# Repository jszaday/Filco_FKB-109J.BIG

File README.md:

# Universa Universis
Retrofit PCB for various Alps full-sized keyboards.

## Planned support:
- AEK (ANSI, EUR, JPN)
- DELL AT101W (ANSI, EUR, JPN)
- DELL AT101 (ANSI, EUR, JPN)
- Strong Man SMK-8851 (BAE, JPN)

## Version History:

### Alpha Revision

Front:

Back:

#### Known Issues
- DELL AT101 support impeded by unpopable popout between RAlt and RCtrl.
- ISO Enter in wrong position (1.5u vs. 1u); can fold down leads of switch to compensate.
- Num pad plus and enter key switches rotated 180° (not a significant issue).
- No LED carrier board.

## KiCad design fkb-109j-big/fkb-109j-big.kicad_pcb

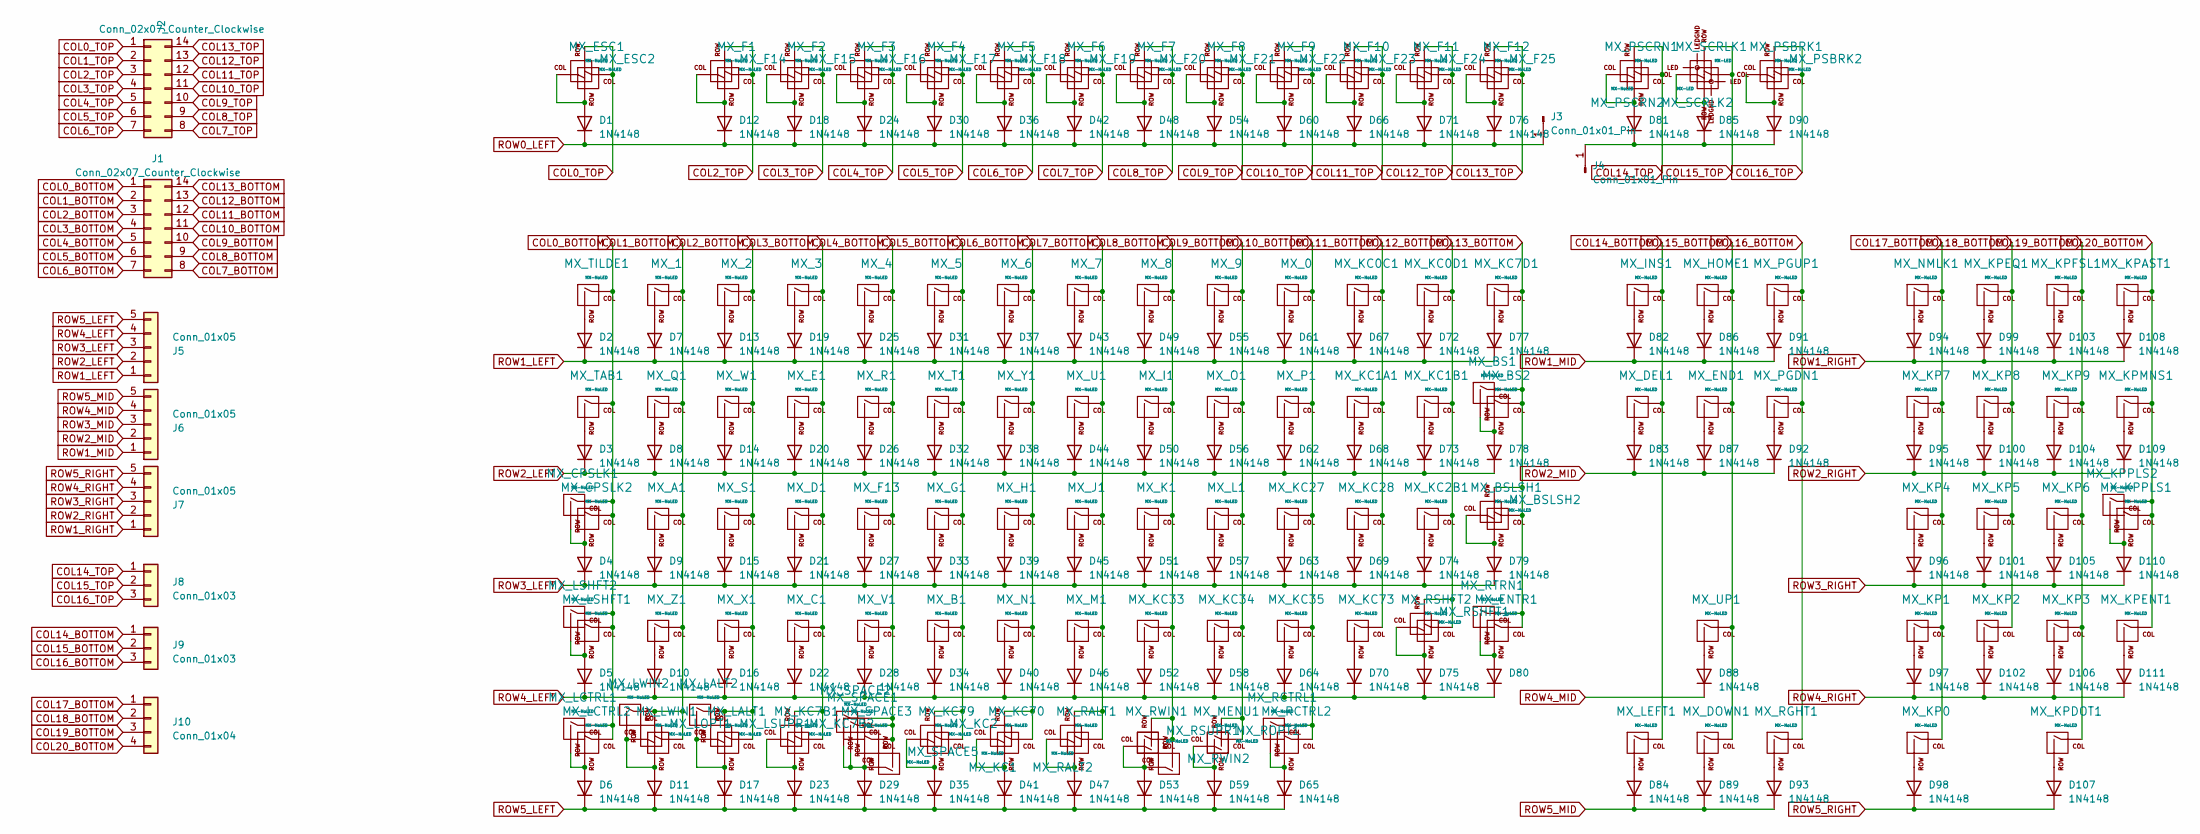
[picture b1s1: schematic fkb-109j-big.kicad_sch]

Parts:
D1, D2, D3, D4, D5, D6, D7, D8, D9, D10, D11, D12, D13, D14, D15, D16, D17, D18, D19, D20, D21, D22, D23, D24, D25, D26, D27, D28, D29, D30, D31, D32, D33, D34, D35, D36, D37, D38, D39, D40, D41, D42, D43, D44, D45, D46, D47, D48, D49, D50, D51, D52, D53, D54, D55, D56, D57, D58, D59, D60, D61, D62, D63, D64, D65, D66, D67, D68, D69, D70, D71, D72, D73, D74, D75, D76, D77, D78, D79, D80, D81, D82, D83, D84, D85, D86, D87, D88, D89, D90, D91, D92, D93, D94, D95, D96, D97, D98, D99, D100, D101, D102, D103, D104, D105, D106, D107, D108, D109, D110, D111: 1N4148; D_DO-35_SOD27_P7.62mm_Horizontal
J1, J2: Conn_02x07_Counter_Clockwise; PinHeader_1x14_P2.00mm_Vertical
J3, J4: Conn_01x01_Pin; PinHeader_1x01_P2.00mm_Vertical
J5, J6, J7: Conn_01x05; PinHeader_1x05_P2.00mm_Vertical
J8, J9: Conn_01x03; PinHeader_1x03_P2.00mm_Vertical
J10: Conn_01x04; PinHeader_1x04_P2.00mm_Vertical
MX_0, MX_1, MX_2, MX_3, MX_4, MX_5, MX_6, MX_7, MX_8, MX_9: MX-NoLED; ALPS-1U
MX_A1: MX-NoLED; ALPS-1U
MX_B1: MX-NoLED; ALPS-1U
MX_BS1: MX-NoLED; ALPS-1U
MX_BS2: MX-NoLED; ALPS-2U
MX_BSLSH1: MX-NoLED; ALPS-1.5U
MX_BSLSH2: MX-NoLED; ALPS-1U
MX_C1: MX-NoLED; ALPS-1U
MX_CPSLK1: MX-NoLED; ALPS-1.5U
MX_CPSLK2: MX-NoLED; ALPS-1.75U
MX_D1: MX-NoLED; ALPS-1U
MX_DEL1: MX-NoLED; ALPS-1U
MX_DOWN1: MX-NoLED; ALPS-1U
MX_E1: MX-NoLED; ALPS-1U
MX_END1: MX-NoLED; ALPS-1U
MX_ENTR1: MX-NoLED; ALPS-2U
MX_ESC1, MX_ESC2: MX-NoLED; ALPS-1U
MX_F1, MX_F2, MX_F3, MX_F4, MX_F5, MX_F6, MX_F7, MX_F8, MX_F9, MX_F10, MX_F11, MX_F12, MX_F13, MX_F14, MX_F15, MX_F16, MX_F17, MX_F18, MX_F19, MX_F20, MX_F21, MX_F22, MX_F23, MX_F24, MX_F25: MX-NoLED; ALPS-1U
MX_G1: MX-NoLED; ALPS-1U
MX_H1: MX-NoLED; ALPS-1U
MX_HOME1: MX-NoLED; ALPS-1U
MX_I1: MX-NoLED; ALPS-1U
MX_INS1: MX-NoLED; ALPS-1U
MX_J1: MX-NoLED; ALPS-1U
MX_K1: MX-NoLED; ALPS-1U
MX_KC0C1, MX_KC0D1, MX_KC1A1, MX_KC1B1, MX_KC2B1, MX_KC7D1, MX_KC27, MX_KC28, MX_KC33, MX_KC34, MX_KC35, MX_KC73: MX-NoLED; ALPS-1U
MX_KC1: MX-NoLED; ALPS-1.5U
MX_KC2, MX_KC7B2: MX-NoLED; ALPS-1.75U
MX_KC7B1, MX_KC70, MX_KC79: MX-NoLED; ALPS-1.25U
MX_KP0: MX-NoLED; ALPS-2U
MX_KP1, MX_KP2, MX_KP3, MX_KP4, MX_KP5, MX_KP6, MX_KP7, MX_KP8, MX_KP9: MX-NoLED; ALPS-1U
MX_KPAST1: MX-NoLED; ALPS-1U
MX_KPDOT1: MX-NoLED; ALPS-1U
MX_KPENT1: MX-NoLED; ALPS-2U
MX_KPEQ1: MX-NoLED; ALPS-1U
MX_KPFSL1: MX-NoLED; ALPS-1U
MX_KPMNS1: MX-NoLED; ALPS-1U
MX_KPPLS1: MX-NoLED; ALPS-1U
MX_KPPLS2: MX-NoLED; ALPS-2U
MX_L1: MX-NoLED; ALPS-1U
MX_LALT1: MX-NoLED; ALPS-1.25U
MX_LALT2: MX-NoLED; ALPS-1.5U
MX_LCTRL1: MX-NoLED; ALPS-1.25U
MX_LCTRL2: MX-NoLED; ALPS-1.5U
MX_LEFT1: MX-NoLED; ALPS-1U
MX_LOPT1: MX-NoLED; ALPS-1.25U
MX_LSHFT1: MX-NoLED; ALPS-2.25U
MX_LSHFT2: MX-NoLED; ALPS-1.25U
MX_LSUPR1: MX-NoLED; ALPS-1.5U
MX_LWIN1: MX-NoLED; ALPS-1.25U
MX_LWIN2: MX-NoLED; ALPS-1U
MX_M1: MX-NoLED; ALPS-1U
MX_MENU1: MX-NoLED; ALPS-1.25U
MX_N1: MX-NoLED; ALPS-1U
MX_NMLK1: MX-NoLED; ALPS-1U
MX_O1: MX-NoLED; ALPS-1U
MX_P1: MX-NoLED; ALPS-1U
MX_PGDN1: MX-NoLED; ALPS-1U
MX_PGUP1: MX-NoLED; ALPS-1U
MX_PSBRK1, MX_PSBRK2: MX-NoLED; ALPS-1U
MX_PSCRN1, MX_PSCRN2: MX-NoLED; ALPS-1U
MX_Q1: MX-NoLED; ALPS-1U
MX_R1: MX-NoLED; ALPS-1U
MX_RALT1: MX-NoLED; ALPS-1.25U
MX_RALT2: MX-NoLED; ALPS-1.5U
MX_RCTRL1: MX-NoLED; ALPS-1.25U
MX_RCTRL2: MX-NoLED; ALPS-1.5U
MX_RGHT1: MX-NoLED; ALPS-1U
MX_ROPT1: MX-NoLED; ALPS-1.25U
MX_RSHFT1: MX-NoLED; ALPS-2.75U
MX_RSHFT2: MX-NoLED; ALPS-1.75U
MX_RSUPR1: MX-NoLED; ALPS-1.5U
MX_RTRN1: MX-NoLED; ALPS-2.25U
MX_RWIN1: MX-NoLED; ALPS-1.25U
MX_RWIN2: MX-NoLED; ALPS-1U
MX_S1: MX-NoLED; ALPS-1U
MX_SCRLK1, MX_SCRLK2: MX-LED; ALPS-1U
MX_SPACE1: MX-NoLED; ALPS-6.5U
MX_SPACE2: MX-NoLED; ALPS-6.25U
MX_SPACE3: MX-NoLED; ALPS-2.5U
MX_SPACE5: MX-NoLED; ALPS-2U
MX_T1: MX-NoLED; ALPS-1U
MX_TAB1: MX-NoLED; ALPS-1.5U
MX_TILDE1: MX-NoLED; ALPS-1U
MX_U1: MX-NoLED; ALPS-1U
MX_UP1: MX-NoLED; ALPS-1U
MX_V1: MX-NoLED; ALPS-1U
MX_W1: MX-NoLED; ALPS-1U
MX_X1: MX-NoLED; ALPS-1U
MX_Y1: MX-NoLED; ALPS-1U
MX_Z1: MX-NoLED; ALPS-1U

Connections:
COL0_BOTTOM: J1.1, MX_CPSLK1.1 (COL), MX_CPSLK2.1 (COL), MX_LCTRL1.1 (COL), MX_LCTRL2.1 (COL), MX_LSHFT1.1 (COL), MX_LSHFT2.1 (COL), MX_TAB1.1 (COL), MX_TILDE1.1 (COL)
COL0_TOP: J2.1, MX_ESC1.1 (COL), MX_ESC2.2 (ROW)
COL1_BOTTOM: J1.2, MX_1.1 (COL), MX_A1.1 (COL), MX_LOPT1.2 (ROW), MX_LWIN1.1 (COL), MX_LWIN2.1 (COL), MX_Q1.1 (COL), MX_Z1.1 (COL)
COL1_TOP: J2.2
COL2_BOTTOM: J1.3, MX_2.1 (COL), MX_LALT1.1 (COL), MX_LALT2.1 (COL), MX_LSUPR1.2 (ROW), MX_S1.1 (COL), MX_W1.1 (COL), MX_X1.1 (COL)
COL2_TOP: J2.3, MX_F1.1 (COL), MX_F14.2 (ROW)
COL3_BOTTOM: J1.4, MX_3.1 (COL), MX_C1.1 (COL), MX_D1.1 (COL), MX_E1.1 (COL), MX_KC7B1.1 (COL), MX_KC7B2.2 (ROW)
COL3_TOP: J2.4, MX_F2.1 (COL), MX_F15.2 (ROW)
COL4_BOTTOM: J1.5, MX_4.1 (COL), MX_F13.1 (COL), MX_R1.1 (COL), MX_SPACE1.1 (COL), MX_SPACE2.1 (COL), MX_SPACE3.1 (COL), MX_SPACE5.2 (ROW), MX_V1.1 (COL)
COL4_TOP: J2.5, MX_F3.1 (COL), MX_F16.2 (ROW)
COL5_BOTTOM: J1.6, MX_5.1 (COL), MX_B1.1 (COL), MX_G1.1 (COL), MX_KC2.2 (ROW), MX_KC79.1 (COL), MX_T1.1 (COL)
COL5_TOP: J2.6, MX_F4.1 (COL), MX_F17.2 (ROW)
COL6_BOTTOM: J1.7, MX_6.1 (COL), MX_H1.1 (COL), MX_KC1.2 (ROW), MX_KC70.1 (COL), MX_N1.1 (COL), MX_Y1.1 (COL)
COL6_TOP: J2.7, MX_F5.1 (COL), MX_F18.2 (ROW)
COL7_BOTTOM: J1.8, MX_7.1 (COL), MX_J1.1 (COL), MX_M1.1 (COL), MX_RALT1.1 (COL), MX_RALT2.2 (ROW), MX_U1.1 (COL)
COL7_TOP: J2.8, MX_F6.1 (COL), MX_F19.2 (ROW)
COL8_BOTTOM: J1.9, MX_8.1 (COL), MX_I1.1 (COL), MX_K1.1 (COL), MX_KC33.1 (COL), MX_RSUPR1.2 (ROW), MX_RWIN1.1 (COL), MX_RWIN2.2 (ROW)
COL8_TOP: J2.9, MX_F7.1 (COL), MX_F20.2 (ROW)
COL9_BOTTOM: J1.10, MX_9.1 (COL), MX_KC34.1 (COL), MX_L1.1 (COL), MX_MENU1.1 (COL), MX_O1.1 (COL), MX_ROPT1.2 (ROW)
COL9_TOP: J2.10, MX_F8.1 (COL), MX_F21.2 (ROW)
COL10_BOTTOM: J1.11, MX_0.1 (COL), MX_KC27.1 (COL), MX_KC35.1 (COL), MX_P1.1 (COL), MX_RCTRL1.1 (COL), MX_RCTRL2.1 (COL)
COL10_TOP: J2.11, MX_F9.1 (COL), MX_F22.2 (ROW)
COL11_BOTTOM: J1.12, MX_KC0C1.1 (COL), MX_KC1A1.1 (COL), MX_KC28.1 (COL), MX_KC73.1 (COL)
COL11_TOP: J2.12, MX_F10.1 (COL), MX_F23.2 (ROW)
COL12_BOTTOM: J1.13, MX_KC0D1.1 (COL), MX_KC1B1.1 (COL), MX_KC2B1.1 (COL), MX_RSHFT1.2 (ROW), MX_RSHFT2.1 (COL)
COL12_TOP: J2.13, MX_F11.1 (COL), MX_F24.2 (ROW)
COL13_BOTTOM: J1.14, MX_BS1.1 (COL), MX_BS2.1 (COL), MX_BSLSH1.1 (COL), MX_BSLSH2.2 (ROW), MX_ENTR1.1 (COL), MX_KC7D1.1 (COL), MX_RTRN1.1 (COL)
COL13_TOP: J2.14, MX_F12.1 (COL), MX_F25.2 (ROW)
COL14_BOTTOM: J9.1, MX_DEL1.1 (COL), MX_INS1.1 (COL), MX_LEFT1.1 (COL)
COL14_TOP: J8.1, MX_PSCRN1.1 (COL), MX_PSCRN2.2 (ROW)
COL15_BOTTOM: J9.2, MX_DOWN1.1 (COL), MX_END1.1 (COL), MX_HOME1.1 (COL), MX_UP1.1 (COL)
COL15_TOP: J8.2, MX_SCRLK1.1 (COL), MX_SCRLK2.2 (ROW)
COL16_BOTTOM: J9.3, MX_PGDN1.1 (COL), MX_PGUP1.1 (COL), MX_RGHT1.1 (COL)
COL16_TOP: J8.3, MX_PSBRK1.1 (COL), MX_PSBRK2.2 (ROW)
COL17_BOTTOM: J10.1, MX_KP0.1 (COL), MX_KP1.1 (COL), MX_KP4.1 (COL), MX_KP7.1 (COL), MX_NMLK1.1 (COL)
COL18_BOTTOM: J10.2, MX_KP2.1 (COL), MX_KP5.1 (COL), MX_KP8.1 (COL), MX_KPEQ1.1 (COL)
COL19_BOTTOM: J10.3, MX_KP3.1 (COL), MX_KP6.1 (COL), MX_KP9.1 (COL), MX_KPDOT1.1 (COL), MX_KPFSL1.1 (COL)
COL20_BOTTOM: J10.4, MX_KPAST1.1 (COL), MX_KPENT1.1 (COL), MX_KPMNS1.1 (COL), MX_KPPLS1.1 (COL), MX_KPPLS2.1 (COL)
unnamed: D1.2 (A), MX_ESC1.2 (ROW), MX_ESC2.1 (COL)
unnamed: D2.2 (A), MX_TILDE1.2 (ROW)
unnamed: D3.2 (A), MX_TAB1.2 (ROW)
unnamed: D4.2 (A), MX_CPSLK1.2 (ROW), MX_CPSLK2.2 (ROW)
unnamed: D5.2 (A), MX_LSHFT1.2 (ROW), MX_LSHFT2.2 (ROW)
unnamed: D6.2 (A), MX_LCTRL1.2 (ROW), MX_LCTRL2.2 (ROW)
unnamed: D7.2 (A), MX_1.2 (ROW)
unnamed: D8.2 (A), MX_Q1.2 (ROW)
unnamed: D9.2 (A), MX_A1.2 (ROW)
unnamed: D10.2 (A), MX_Z1.2 (ROW)
unnamed: D11.2 (A), MX_LOPT1.1 (COL), MX_LWIN1.2 (ROW), MX_LWIN2.2 (ROW)
unnamed: D12.2 (A), MX_F1.2 (ROW), MX_F14.1 (COL)
unnamed: D13.2 (A), MX_2.2 (ROW)
unnamed: D14.2 (A), MX_W1.2 (ROW)
unnamed: D15.2 (A), MX_S1.2 (ROW)
unnamed: D16.2 (A), MX_X1.2 (ROW)
unnamed: D17.2 (A), MX_LALT1.2 (ROW), MX_LALT2.2 (ROW), MX_LSUPR1.1 (COL)
unnamed: D18.2 (A), MX_F2.2 (ROW), MX_F15.1 (COL)
unnamed: D19.2 (A), MX_3.2 (ROW)
unnamed: D20.2 (A), MX_E1.2 (ROW)
unnamed: D21.2 (A), MX_D1.2 (ROW)
unnamed: D22.2 (A), MX_C1.2 (ROW)
unnamed: D23.2 (A), MX_KC7B1.2 (ROW), MX_KC7B2.1 (COL)
unnamed: D24.2 (A), MX_F3.2 (ROW), MX_F16.1 (COL)
unnamed: D25.2 (A), MX_4.2 (ROW)
unnamed: D26.2 (A), MX_R1.2 (ROW)
unnamed: D27.2 (A), MX_F13.2 (ROW)
unnamed: D28.2 (A), MX_V1.2 (ROW)
unnamed: D29.2 (A), MX_SPACE1.2 (ROW), MX_SPACE2.2 (ROW), MX_SPACE3.2 (ROW), MX_SPACE5.1 (COL)
unnamed: D30.2 (A), MX_F4.2 (ROW), MX_F17.1 (COL)
unnamed: D31.2 (A), MX_5.2 (ROW)
unnamed: D32.2 (A), MX_T1.2 (ROW)
unnamed: D33.2 (A), MX_G1.2 (ROW)
unnamed: D34.2 (A), MX_B1.2 (ROW)
unnamed: D35.2 (A), MX_KC2.1 (COL), MX_KC79.2 (ROW)
unnamed: D36.2 (A), MX_F5.2 (ROW), MX_F18.1 (COL)
unnamed: D37.2 (A), MX_6.2 (ROW)
unnamed: D38.2 (A), MX_Y1.2 (ROW)
unnamed: D39.2 (A), MX_H1.2 (ROW)
unnamed: D40.2 (A), MX_N1.2 (ROW)
unnamed: D41.2 (A), MX_KC1.1 (COL), MX_KC70.2 (ROW)
unnamed: D42.2 (A), MX_F6.2 (ROW), MX_F19.1 (COL)
unnamed: D43.2 (A), MX_7.2 (ROW)
unnamed: D44.2 (A), MX_U1.2 (ROW)
unnamed: D45.2 (A), MX_J1.2 (ROW)
unnamed: D46.2 (A), MX_M1.2 (ROW)
unnamed: D47.2 (A), MX_RALT1.2 (ROW), MX_RALT2.1 (COL)
unnamed: D48.2 (A), MX_F7.2 (ROW), MX_F20.1 (COL)
unnamed: D49.2 (A), MX_8.2 (ROW)
unnamed: D50.2 (A), MX_I1.2 (ROW)
unnamed: D51.2 (A), MX_K1.2 (ROW)
unnamed: D52.2 (A), MX_KC33.2 (ROW)
unnamed: D53.2 (A), MX_RSUPR1.1 (COL), MX_RWIN1.2 (ROW), MX_RWIN2.1 (COL)
unnamed: D54.2 (A), MX_F8.2 (ROW), MX_F21.1 (COL)
unnamed: D55.2 (A), MX_9.2 (ROW)
unnamed: D56.2 (A), MX_O1.2 (ROW)
unnamed: D57.2 (A), MX_L1.2 (ROW)
unnamed: D58.2 (A), MX_KC34.2 (ROW)
unnamed: D59.2 (A), MX_MENU1.2 (ROW), MX_ROPT1.1 (COL)
unnamed: D60.2 (A), MX_F9.2 (ROW), MX_F22.1 (COL)
unnamed: D61.2 (A), MX_0.2 (ROW)
unnamed: D62.2 (A), MX_P1.2 (ROW)
unnamed: D63.2 (A), MX_KC27.2 (ROW)
unnamed: D64.2 (A), MX_KC35.2 (ROW)
unnamed: D65.2 (A), MX_RCTRL1.2 (ROW), MX_RCTRL2.2 (ROW)
unnamed: D66.2 (A), MX_F10.2 (ROW), MX_F23.1 (COL)
unnamed: D67.2 (A), MX_KC0C1.2 (ROW)
unnamed: D68.2 (A), MX_KC1A1.2 (ROW)
unnamed: D69.2 (A), MX_KC28.2 (ROW)
unnamed: D70.2 (A), MX_KC73.2 (ROW)
unnamed: D71.2 (A), MX_F11.2 (ROW), MX_F24.1 (COL)
unnamed: D72.2 (A), MX_KC0D1.2 (ROW)
unnamed: D73.2 (A), MX_KC1B1.2 (ROW)
unnamed: D74.2 (A), MX_KC2B1.2 (ROW)
unnamed: D75.2 (A), MX_RSHFT1.1 (COL), MX_RSHFT2.2 (ROW)
unnamed: D76.2 (A), MX_F12.2 (ROW), MX_F25.1 (COL)
unnamed: D77.2 (A), MX_KC7D1.2 (ROW)
unnamed: D78.2 (A), MX_BS1.2 (ROW), MX_BS2.2 (ROW)
unnamed: D79.2 (A), MX_BSLSH1.2 (ROW), MX_BSLSH2.1 (COL)
unnamed: D80.2 (A), MX_ENTR1.2 (ROW), MX_RTRN1.2 (ROW)
unnamed: D81.2 (A), MX_PSCRN1.2 (ROW), MX_PSCRN2.1 (COL)
unnamed: D81.1 (K), D85.1 (K), D90.1 (K), J4.1
unnamed: D82.2 (A), MX_INS1.2 (ROW)
unnamed: D83.2 (A), MX_DEL1.2 (ROW)
unnamed: D84.2 (A), MX_LEFT1.2 (ROW)
unnamed: D85.2 (A), MX_SCRLK1.2 (ROW), MX_SCRLK2.1 (COL)
unnamed: D86.2 (A), MX_HOME1.2 (ROW)
unnamed: D87.2 (A), MX_END1.2 (ROW)
unnamed: D88.2 (A), MX_UP1.2 (ROW)
unnamed: D89.2 (A), MX_DOWN1.2 (ROW)
unnamed: D90.2 (A), MX_PSBRK1.2 (ROW), MX_PSBRK2.1 (COL)
unnamed: D91.2 (A), MX_PGUP1.2 (ROW)
unnamed: D92.2 (A), MX_PGDN1.2 (ROW)
unnamed: D93.2 (A), MX_RGHT1.2 (ROW)
unnamed: D94.2 (A), MX_NMLK1.2 (ROW)
unnamed: D95.2 (A), MX_KP7.2 (ROW)
unnamed: D96.2 (A), MX_KP4.2 (ROW)
unnamed: D97.2 (A), MX_KP1.2 (ROW)
unnamed: D98.2 (A), MX_KP0.2 (ROW)
unnamed: D99.2 (A), MX_KPEQ1.2 (ROW)
unnamed: D100.2 (A), MX_KP8.2 (ROW)
unnamed: D101.2 (A), MX_KP5.2 (ROW)
unnamed: D102.2 (A), MX_KP2.2 (ROW)
unnamed: D103.2 (A), MX_KPFSL1.2 (ROW)
unnamed: D104.2 (A), MX_KP9.2 (ROW)
unnamed: D105.2 (A), MX_KP6.2 (ROW)
unnamed: D106.2 (A), MX_KP3.2 (ROW)
unnamed: D107.2 (A), MX_KPDOT1.2 (ROW)
unnamed: D108.2 (A), MX_KPAST1.2 (ROW)
unnamed: D109.2 (A), MX_KPMNS1.2 (ROW)
unnamed: D110.2 (A), MX_KPPLS1.2 (ROW), MX_KPPLS2.2 (ROW)
unnamed: D111.2 (A), MX_KPENT1.2 (ROW)
ROW0_LEFT: D1.1 (K), D12.1 (K), D18.1 (K), D24.1 (K), D30.1 (K), D36.1 (K), D42.1 (K), D48.1 (K), D54.1 (K), D60.1 (K), D66.1 (K), D71.1 (K), D76.1 (K), J3.1
ROW1_LEFT: D2.1 (K), D7.1 (K), D13.1 (K), D19.1 (K), D25.1 (K), D31.1 (K), D37.1 (K), D43.1 (K), D49.1 (K), D55.1 (K), D61.1 (K), D67.1 (K), D72.1 (K), D77.1 (K), J5.1
ROW1_MID: D82.1 (K), D86.1 (K), D91.1 (K), J6.1
ROW1_RIGHT: D94.1 (K), D99.1 (K), D103.1 (K), D108.1 (K), J7.1
ROW2_LEFT: D3.1 (K), D8.1 (K), D14.1 (K), D20.1 (K), D26.1 (K), D32.1 (K), D38.1 (K), D44.1 (K), D50.1 (K), D56.1 (K), D62.1 (K), D68.1 (K), D73.1 (K), D78.1 (K), J5.2
ROW2_MID: D83.1 (K), D87.1 (K), D92.1 (K), J6.2
ROW2_RIGHT: D95.1 (K), D100.1 (K), D104.1 (K), D109.1 (K), J7.2
ROW3_LEFT: D4.1 (K), D9.1 (K), D15.1 (K), D21.1 (K), D27.1 (K), D33.1 (K), D39.1 (K), D45.1 (K), D51.1 (K), D57.1 (K), D63.1 (K), D69.1 (K), D74.1 (K), D79.1 (K), J5.3
ROW3_MID: J6.3
ROW3_RIGHT: D96.1 (K), D101.1 (K), D105.1 (K), D110.1 (K), J7.3
ROW4_LEFT: D5.1 (K), D10.1 (K), D16.1 (K), D22.1 (K), D28.1 (K), D34.1 (K), D40.1 (K), D46.1 (K), D52.1 (K), D58.1 (K), D64.1 (K), D70.1 (K), D75.1 (K), D80.1 (K), J5.4
ROW4_MID: D88.1 (K), J6.4
ROW4_RIGHT: D97.1 (K), D102.1 (K), D106.1 (K), D111.1 (K), J7.4
ROW5_LEFT: D6.1 (K), D11.1 (K), D17.1 (K), D23.1 (K), D29.1 (K), D35.1 (K), D41.1 (K), D47.1 (K), D53.1 (K), D59.1 (K), D65.1 (K), J5.5
ROW5_MID: D84.1 (K), D89.1 (K), D93.1 (K), J6.5
ROW5_RIGHT: D98.1 (K), D107.1 (K), J7.5

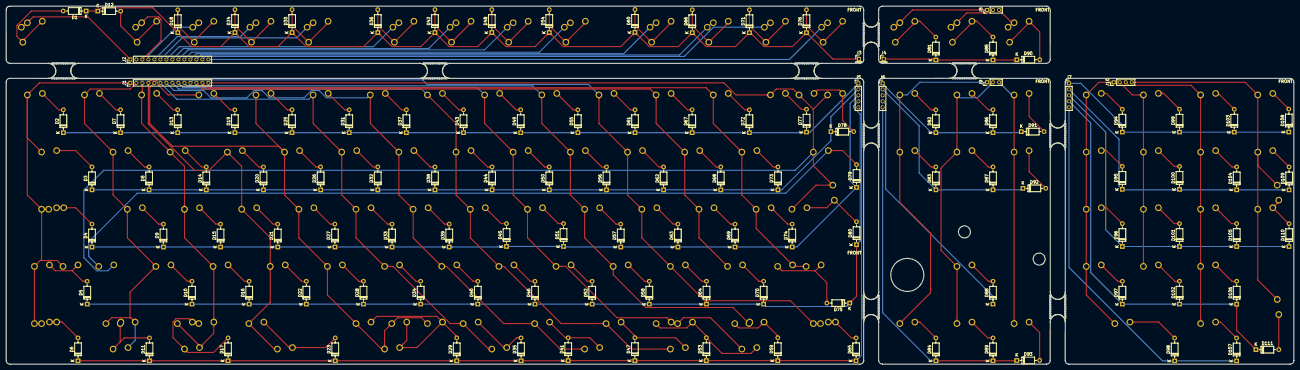
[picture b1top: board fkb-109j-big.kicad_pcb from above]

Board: 2 copper layers, 429.1 x 119.3 mm, 280 parts (0 on the bottom side), 164 nets.

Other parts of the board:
mouse-bite-5mm-slot, mouse-bite-5mm-slot#2, mouse-bite-5mm-slot#3, mouse-bite-5mm-slot#4, mouse-bite-5mm-slot#5, mouse-bite-5mm-slot#6, mouse-bite-5mm-slot#7, mouse-bite-5mm-slot#8, mouse-bite-5mm-slot#9: VAL**; mouse-bite-5mm-slot

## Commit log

2023-04-23 initialize project
2023-04-24 Start establishing layout
2023-04-24 start board layout
2023-04-25 continue layout
2023-04-25 fix footprint
2023-04-25 finish preliminary layout
2023-04-25 start moving diodes
2023-04-25 add 7u/jis bottom-row
2023-04-25 continue placing diodes
2023-04-25 finish preliminary diode placement.
2023-04-26 panelize all the things
2023-04-26 layout cont.
2023-04-27 layout... done?
2023-04-28 add some holes.
2023-04-28 add umu; minor cleanup.
2023-04-28 start rounding corners
2023-04-29 finish rounding out corners.
2023-04-29 add teardrops.
2023-05-22 add images
